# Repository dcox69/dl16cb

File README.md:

# Alientek DL16 (Plus) Connection Board

This project is a small adapter board for the Alientek DL16 (Plus) logic analyzer, which I find more convenient than the cables that come with the device.

It’s a single-sided PCB housed in a half-size enclosure. I used the top side (F-Cu) for the markings.

To make the PCB, I used the iron-on transfer technique with a laser printer. First, I transferred the B-Cu layer. Then I etched the PCB with iron perchloride. Next, I drilled the holes, then transferred the F-Cu (the labels) onto the front side. I soldered the connectors, then applied a protective coating to both sides.

For the half-case, I used brass thermal inserts and 4mm M2 screws.

This was a project I completed very quickly; it took just 3 hours from the initial idea to completion.

[Connectors](https://www.aliexpress.com/item/4000873858801.html)

[Alientek DL16 (Plus)](https://en.alientek.com/Product_Details/44.html)

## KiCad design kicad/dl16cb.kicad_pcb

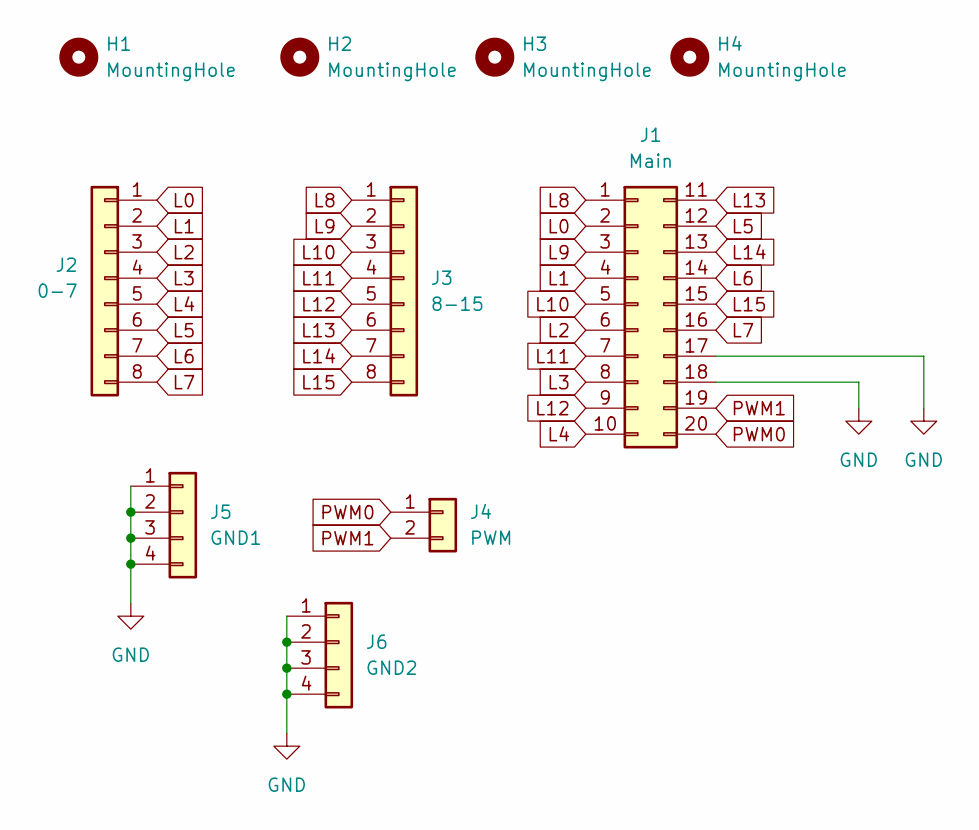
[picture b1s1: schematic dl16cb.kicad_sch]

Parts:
H1, H2, H3, H4: MountingHole; MountingHole_2.7mm_M2.5
J1: Main; PinHeader_2x10_P2.54mm_Vertical
J2: 0-7; PinHeader_1x08_P2.54mm_Vertical
J3: 8-15; PinHeader_1x08_P2.54mm_Vertical
J4: PWM; PinHeader_1x02_P2.54mm_Vertical
J5: GND1; PinHeader_1x04_P2.54mm_Vertical
J6: GND2; PinHeader_1x04_P2.54mm_Vertical

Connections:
GND: J1.17, J1.18, J5.1, J5.2, J5.3, J5.4, J6.1, J6.2, J6.3, J6.4
L0: J1.2, J2.1
L1: J1.4, J2.2
L2: J1.6, J2.3
L3: J1.8, J2.4
L4: J1.10, J2.5
L5: J1.12, J2.6
L6: J1.14, J2.7
L7: J1.16, J2.8
L8: J1.1, J3.1
L9: J1.3, J3.2
L10: J1.5, J3.3
L11: J1.7, J3.4
L12: J1.9, J3.5
L13: J1.11, J3.6
L14: J1.13, J3.7
L15: J1.15, J3.8
PWM0: J1.20, J4.1
PWM1: J1.19, J4.2

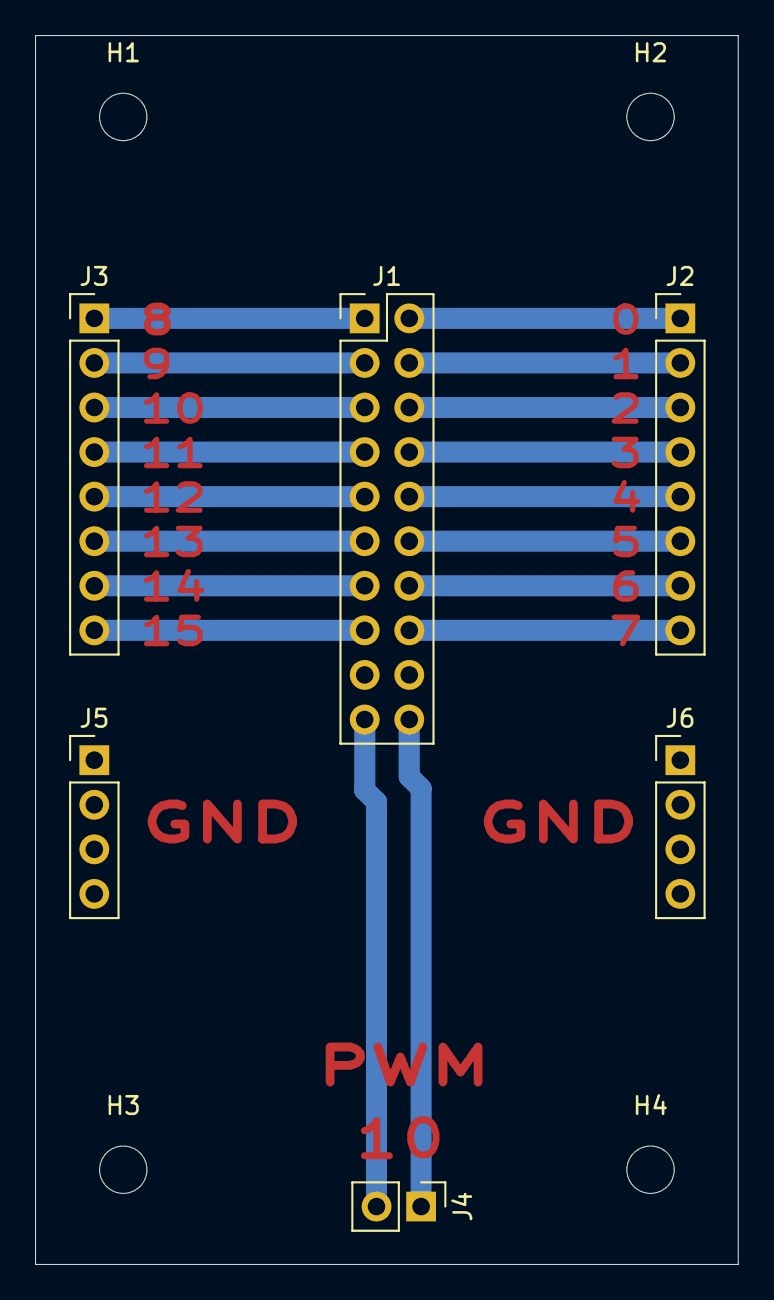
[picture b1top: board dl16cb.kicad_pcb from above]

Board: 2 copper layers, 40.1 x 70.0 mm, 10 parts (0 on the bottom side), 19 nets.
